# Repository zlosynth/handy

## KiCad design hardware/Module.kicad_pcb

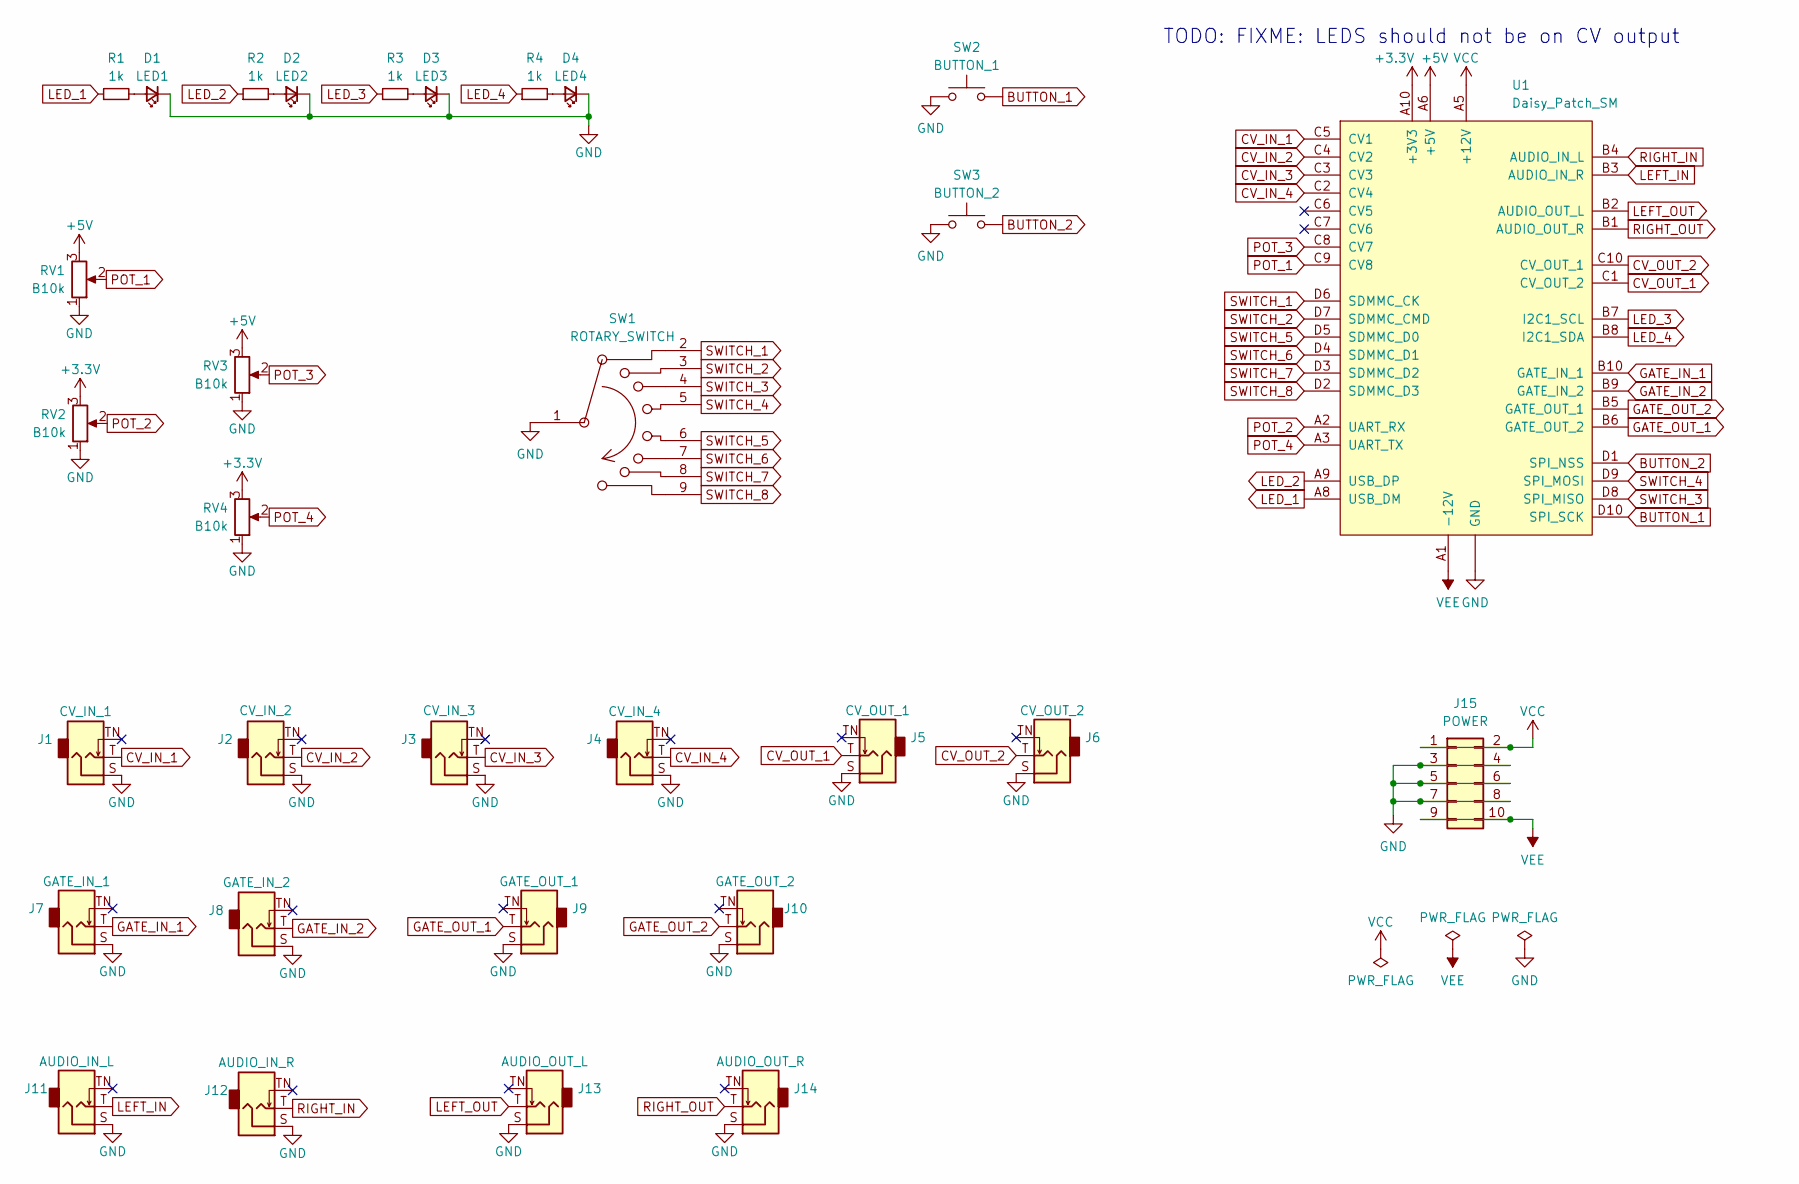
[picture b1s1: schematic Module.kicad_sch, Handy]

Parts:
D1: LED1; LED_D3.0mm
D2: LED2; LED_D3.0mm
D3: LED3; LED_D3.0mm
D4: LED4; LED_D3.0mm
J1: CV_IN_1; Jack_3.5mm_QingPu_WQP-PJ398SM_Vertical_CircularHoles
J2: CV_IN_2; Jack_3.5mm_QingPu_WQP-PJ398SM_Vertical_CircularHoles
J3: CV_IN_3; Jack_3.5mm_QingPu_WQP-PJ398SM_Vertical_CircularHoles
J4: CV_IN_4; Jack_3.5mm_QingPu_WQP-PJ398SM_Vertical_CircularHoles
J5: CV_OUT_1; Jack_3.5mm_QingPu_WQP-PJ398SM_Vertical_CircularHoles
J6: CV_OUT_2; Jack_3.5mm_QingPu_WQP-PJ398SM_Vertical_CircularHoles
J7: GATE_IN_1; Jack_3.5mm_QingPu_WQP-PJ398SM_Vertical_CircularHoles
J8: GATE_IN_2; Jack_3.5mm_QingPu_WQP-PJ398SM_Vertical_CircularHoles
J9: GATE_OUT_1; Jack_3.5mm_QingPu_WQP-PJ398SM_Vertical_CircularHoles
J10: GATE_OUT_2; Jack_3.5mm_QingPu_WQP-PJ398SM_Vertical_CircularHoles
J11: AUDIO_IN_L; Jack_3.5mm_QingPu_WQP-PJ398SM_Vertical_CircularHoles
J12: AUDIO_IN_R; Jack_3.5mm_QingPu_WQP-PJ398SM_Vertical_CircularHoles
J13: AUDIO_OUT_L; Jack_3.5mm_QingPu_WQP-PJ398SM_Vertical_CircularHoles
J14: AUDIO_OUT_R; Jack_3.5mm_QingPu_WQP-PJ398SM_Vertical_CircularHoles
J15: POWER; PinHeader_2x05_P2.54mm_Vertical
R1, R2, R3, R4: 1k; R_0805_2012Metric_Pad1.20x1.40mm_HandSolder
RV1, RV3: B10k; Potentiometer_Thonk_Trimmer
RV2, RV4: B10k; Potentiometer_Alpha_RD901F-40-00D_Single_Vertical
SW1: ROTARY_SWITCH; Rotary_Switch_8_Alpha
SW2: BUTTON_1; SW_PUSH_6mm
SW3: BUTTON_2; SW_PUSH_6mm
U1: Daisy_Patch_SM

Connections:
+3.3V: RV2.3, RV4.3, U1.A10 (+3V3)
+5V: RV1.3, RV3.3, U1.A6 (+5V)
BUTTON_1: SW2.2, U1.D10 (SPI_SCK)
BUTTON_2: SW3.2, U1.D1 (SPI_NSS)
CV_IN_1: J1.T, U1.C5 (CV1)
CV_IN_2: J2.T, U1.C4 (CV2)
CV_IN_3: J3.T, U1.C3 (CV3)
CV_IN_4: J4.T, U1.C2 (CV4)
CV_OUT_1: J5.T, U1.C1 (CV_OUT_2)
CV_OUT_2: J6.T, U1.C10 (CV_OUT_1)
GATE_IN_1: J7.T, U1.B10 (GATE_IN_1)
GATE_IN_2: J8.T, U1.B9 (GATE_IN_2)
GATE_OUT_1: J9.T, U1.B6 (GATE_OUT_2)
GATE_OUT_2: J10.T, U1.B5 (GATE_OUT_1)
GND: D1.1 (K), D2.1 (K), D3.1 (K), D4.1 (K), J1.S, J2.S, J3.S, J4.S, J5.S, J6.S, J7.S, J8.S, J9.S, J10.S, J11.S, J12.S, J13.S, J14.S, J15.3, J15.4, J15.5, J15.6, J15.7, J15.8, RV1.1, RV2.1, RV3.1, RV4.1, SW1.1, SW2.1, SW3.1, U1.A4 (GND), U1.A7 (GND)
LED_1: R1.1, U1.A8 (USB_DM)
LED_2: R2.1, U1.A9 (USB_DP)
LED_3: R3.1, U1.B7 (I2C1_SCL)
LED_4: R4.1, U1.B8 (I2C1_SDA)
LEFT_IN: J11.T, U1.B3 (AUDIO_IN_R)
LEFT_OUT: J13.T, U1.B2 (AUDIO_OUT_L)
unnamed: D1.2 (A), R1.2
unnamed: D2.2 (A), R2.2
unnamed: D3.2 (A), R3.2
unnamed: D4.2 (A), R4.2
POT_1: RV1.2, U1.C9 (CV8)
POT_2: RV2.2, U1.A2 (UART_RX)
POT_3: RV3.2, U1.C8 (CV7)
POT_4: RV4.2, U1.A3 (UART_TX)
RIGHT_IN: J12.T, U1.B4 (AUDIO_IN_L)
RIGHT_OUT: J14.T, U1.B1 (AUDIO_OUT_R)
SWITCH_1: SW1.2, U1.D6 (SDMMC_CK)
SWITCH_2: SW1.3, U1.D7 (SDMMC_CMD)
SWITCH_3: SW1.4, U1.D8 (SPI_MISO)
SWITCH_4: SW1.5, U1.D9 (SPI_MOSI)
SWITCH_5: SW1.6, U1.D5 (SDMMC_D0)
SWITCH_6: SW1.7, U1.D4 (SDMMC_D1)
SWITCH_7: SW1.8, U1.D3 (SDMMC_D2)
SWITCH_8: SW1.9, U1.D2 (SDMMC_D3)
VCC: J15.1, J15.2, U1.A5 (+12V)
VEE: J15.9, J15.10, U1.A1 (-12V)

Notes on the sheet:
TODO: FIXME: LEDS should not be on CV output

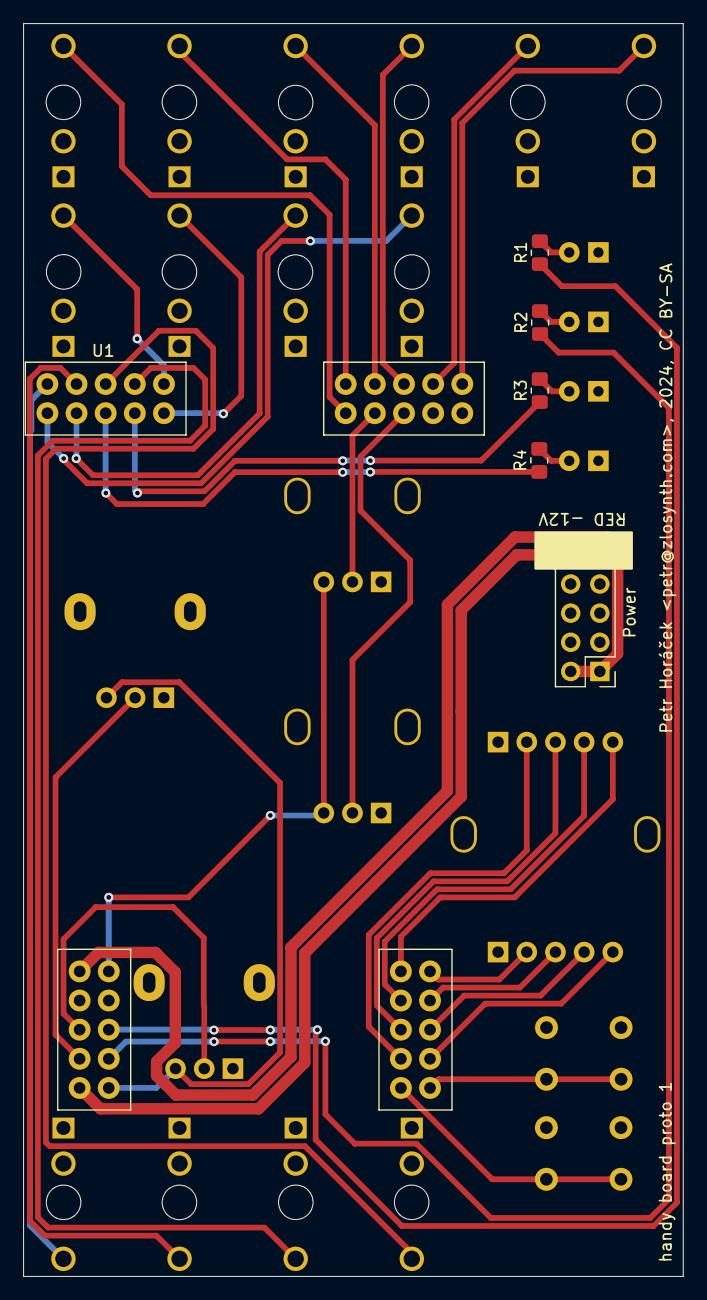
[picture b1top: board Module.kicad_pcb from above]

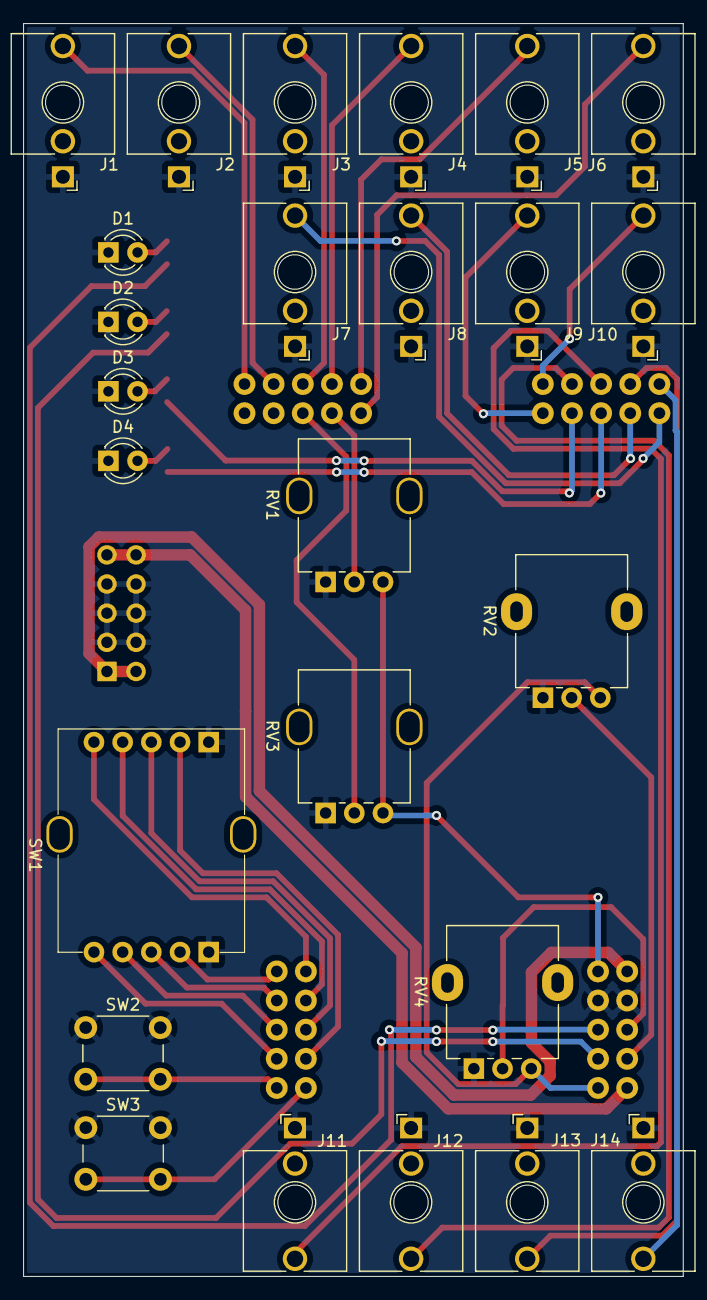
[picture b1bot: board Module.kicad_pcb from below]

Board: 2 copper layers, 57.5 x 109.2 mm, 31 parts (25 on the bottom side), 41 nets.

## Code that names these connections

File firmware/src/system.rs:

pub use stm32h7xx_hal as hal;

use daisy::led::LedUser;
use fugit::Hertz;
use hal::adc::{AdcSampleTime, Resolution};
use hal::delay::DelayFromCountDownTimer;
use hal::pac::CorePeripherals;
use hal::pac::Peripherals as DevicePeripherals;
use hal::prelude::*;
use systick_monotonic::Systick;

use crate::audio::AudioInterface;
use crate::control_input::{
    ButtonsPins as ControlInputButtonsPins, Config as ControlInputConfig, ControlInputInterface,
    CvsPins as ControlInputCvsPins, GatesPins as ControlInputGatesPins,
    PotsPins as ControlInputPotsPins, SwitchPins as ControlInputSwitchPins,
};
use crate::control_output::{
    Config as ControlOutputConfig, ControlOutputInterface, Pins as ControlOutputPins,
};
use crate::random_generator::RandomGenerator;

pub struct System {
    pub frequency: Hertz<u32>,
    pub mono: Systick<1000>,
    pub status_led: LedUser,
    pub random_generator: RandomGenerator,
    pub audio_interface: AudioInterface,
    pub control_input_interface: ControlInputInterface,
    pub control_output_interface: ControlOutputInterface,
}

impl System {
    /// Initialize system abstraction.
    ///
    /// # Panics
    ///
    /// The system can be initialized only once. It panics otherwise.
    pub fn init(mut cp: CorePeripherals, dp: DevicePeripherals) -> Self {
        enable_cache(&mut cp);

        let board = daisy::Board::take().unwrap();
        let ccdr = daisy::board_freeze_clocks!(board, dp);
        let pins = daisy::board_split_gpios!(board, ccdr, dp);

        let system_frequency = ccdr.clocks.sys_ck();
        let mono = Systick::new(cp.SYST, system_frequency.raw());
        let status_led = daisy::board_split_leds!(pins).USER;
        let random_generator =
            RandomGenerator::from_rng(dp.RNG.constrain(ccdr.peripheral.RNG, &ccdr.clocks));
        let audio_interface = AudioInterface::new(daisy::board_split_audio!(ccdr, pins));
        let mut delay = DelayFromCountDownTimer::new(dp.TIM2.timer(
            100.Hz(),
            ccdr.peripheral.TIM2,
            &ccdr.clocks,
        ));
        let control_input_interface = {
            let (adc_1, adc_2) = {
                let (mut adc_1, mut adc_2) = hal::adc::adc12(
                    dp.ADC1,
                    dp.ADC2,
                    4.MHz(),
                    &mut delay,
                    ccdr.peripheral.ADC12,
                    &ccdr.clocks,
                );
                adc_1.set_resolution(Resolution::SixteenBit);
                adc_1.set_sample_time(AdcSampleTime::T_16);
                adc_2.set_resolution(Resolution::SixteenBit);
                adc_2.set_sample_time(AdcSampleTime::T_16);
                (adc_1.enable(), adc_2.enable())
            };
            ControlInputInterface::new(ControlInputConfig {
                buttons_pins: ControlInputButtonsPins {
                    button_1: pins.GPIO.PIN_D10.into_pull_up_input(),
                    button_2: pins.GPIO.PIN_D1.into_pull_up_input(),
                },
                pots_pins: ControlInputPotsPins {
                    pot_1: pins.GPIO.PIN_C9.into_analog(),
                    pot_2: pins.GPIO.PIN_A2.into_analog(),
                    pot_3: pins.GPIO.PIN_C8.into_analog(),
                    pot_4: pins.GPIO.PIN_A3.into_analog(),
                },
                cvs_pins: ControlInputCvsPins {
                    cv_1: pins.GPIO.PIN_C5.into_analog(),
                    cv_2: pins.GPIO.PIN_C4.into_analog(),
                    cv_3: pins.GPIO.PIN_C3.into_analog(),
                    cv_4: pins.GPIO.PIN_C2.into_analog(),
                },
                gates_pins: ControlInputGatesPins {
                    gate_1: pins.GPIO.PIN_B10.into_floating_input(),
                    gate_2: pins.GPIO.PIN_B9.into_floating_input(),
                },
                switch_pins: ControlInputSwitchPins {
                    switch_1: pins.GPIO.PIN_D6.into_pull_up_input(),
                    switch_2: pins.GPIO.PIN_D7.into_pull_up_input(),
                    switch_3: pins.GPIO.PIN_D8.into_pull_up_input(),
                    switch_4: pins.GPIO.PIN_D9.into_pull_up_input(),
                    switch_5: pins.GPIO.PIN_D5.into_pull_up_input(),
                    switch_6: pins.GPIO.PIN_D4.into_pull_up_input(),
                    switch_7: pins.GPIO.PIN_D3.into_pull_up_input(),
                    switch_8: pins.GPIO.PIN_D2.into_pull_up_input(),
                },
                adc_1,
                adc_2,
            })
        };
        let control_output_interface = {
            let (dac1, dac2) = dp
                .DAC
                .dac((pins.GPIO.PIN_C10, pins.GPIO.PIN_C1), ccdr.peripheral.DAC12);
            let dac1 = dac1.calibrate_buffer(&mut delay).enable();
            let dac2 = dac2.calibrate_buffer(&mut delay).enable();
            ControlOutputInterface::new(ControlOutputConfig {
                pins: ControlOutputPins {
                    leds: (
                        pins.GPIO.PIN_A9.into_push_pull_output(),
                        pins.GPIO.PIN_A8.into_push_pull_output(),
                        pins.GPIO.PIN_B7.into_push_pull_output(),
                        pins.GPIO.PIN_B8.into_push_pull_output(),
                    ),
                    gates: (
                        pins.GPIO.PIN_B6.into_push_pull_output(),
                        pins.GPIO.PIN_B5.into_push_pull_output(),
                    ),
                },
                dac: (dac1, dac2),
            })
        };

        Self {
            frequency: system_frequency,
            mono,
            status_led,
            random_generator,
            audio_interface,
            control_input_interface,
            control_output_interface,
        }
    }
}

/// AN5212: Improve application performance when fetching instruction and
/// data, from both internal andexternal memories.
fn enable_cache(cp: &mut CorePeripherals) {
    cp.SCB.enable_icache();
    // NOTE: This requires cache management around all use of DMA.
    cp.SCB.enable_dcache(&mut cp.CPUID);
}

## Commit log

2024-09-17 Initialize with a README
2024-09-18 Complete panel component placement on pcb
2024-09-18 Patch a rough schematic
2024-09-18 First wire up of the PCB
2024-09-18 Complete the ground plane and fix ERC
2024-09-18 Fix trimmer footprint
2024-09-19 Fix orientation of PCB label
2024-09-19 Fix power connector direction
2024-09-29 Fix LED daisy connection
2024-10-30 Add a stub of rust firmware
2024-10-30 Basic firmware implementation with clock
2024-11-02 Implement steady CV and attenuator

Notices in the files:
hardware/Module.kicad_pcb:
Petr Horáček , 2024, CC BY-SA
hardware/Module.kicad_sch:
CC BY-SA
